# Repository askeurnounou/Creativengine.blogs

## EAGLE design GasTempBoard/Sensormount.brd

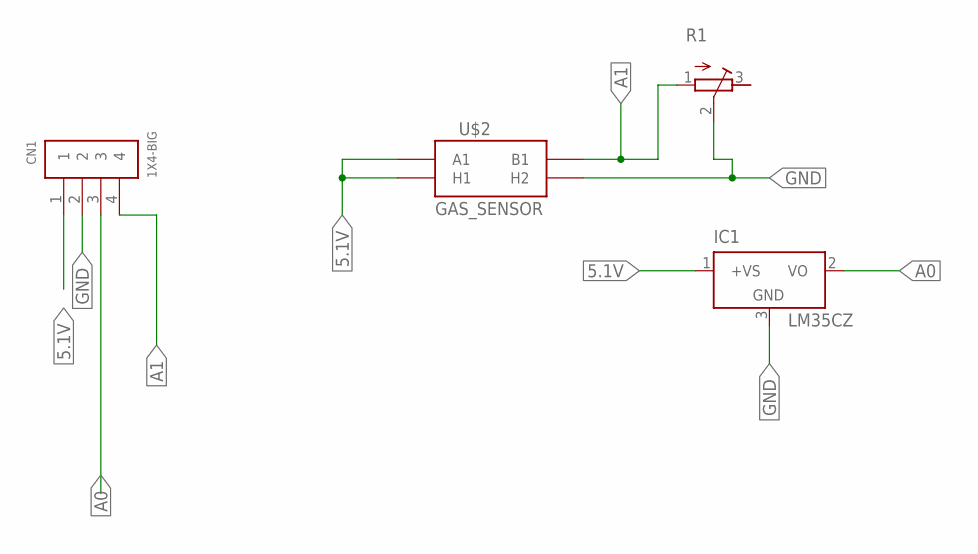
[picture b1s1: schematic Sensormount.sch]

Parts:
CN1: 1X4-BIG; 1X04-BIG
IC1: LM35CZ; TO92
R1: R-TRIMM64W; RTRIM64W
U$2: GAS_SENSOR; MQ-3

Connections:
5.1V: CN1.1, IC1.1 (+VS), U$2.A1, U$2.HA (H1)
A0: CN1.3, IC1.2 (VO)
A1: CN1.4, R1.1 (A), U$2.B1
GND: CN1.2, IC1.3 (GND), R1.2 (S), U$2.HB (H2)

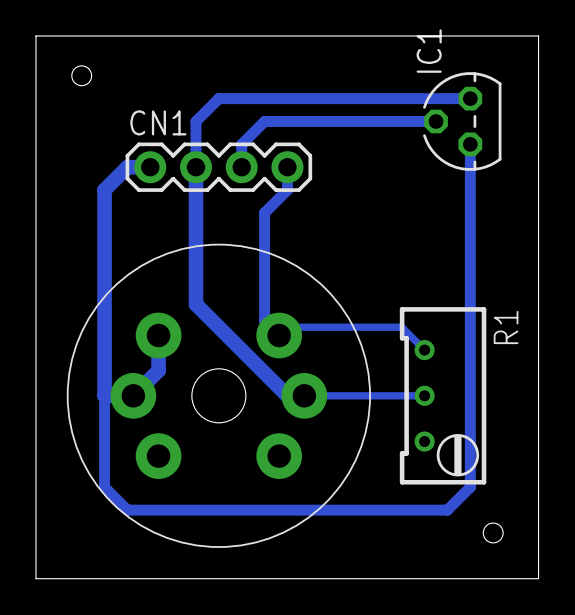
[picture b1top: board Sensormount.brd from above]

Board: 2 copper layers, 27.9 x 30.1 mm, 4 parts (0 on the bottom side), 4 nets.

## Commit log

2015-03-21 :circus_tent: Added .gitattributes & .gitignore files
2015-03-21 Arduino2Proteous
    for download
2015-03-21 Making arduino blink using one liner
2015-05-09 Files for PCB
2015-05-09 Eagle board and schematic file
    Eagle board and schematic file
2015-05-09 GasTempBoard
    Schematic and board files
2015-05-09 Readme
2015-05-09 Sourcecode
